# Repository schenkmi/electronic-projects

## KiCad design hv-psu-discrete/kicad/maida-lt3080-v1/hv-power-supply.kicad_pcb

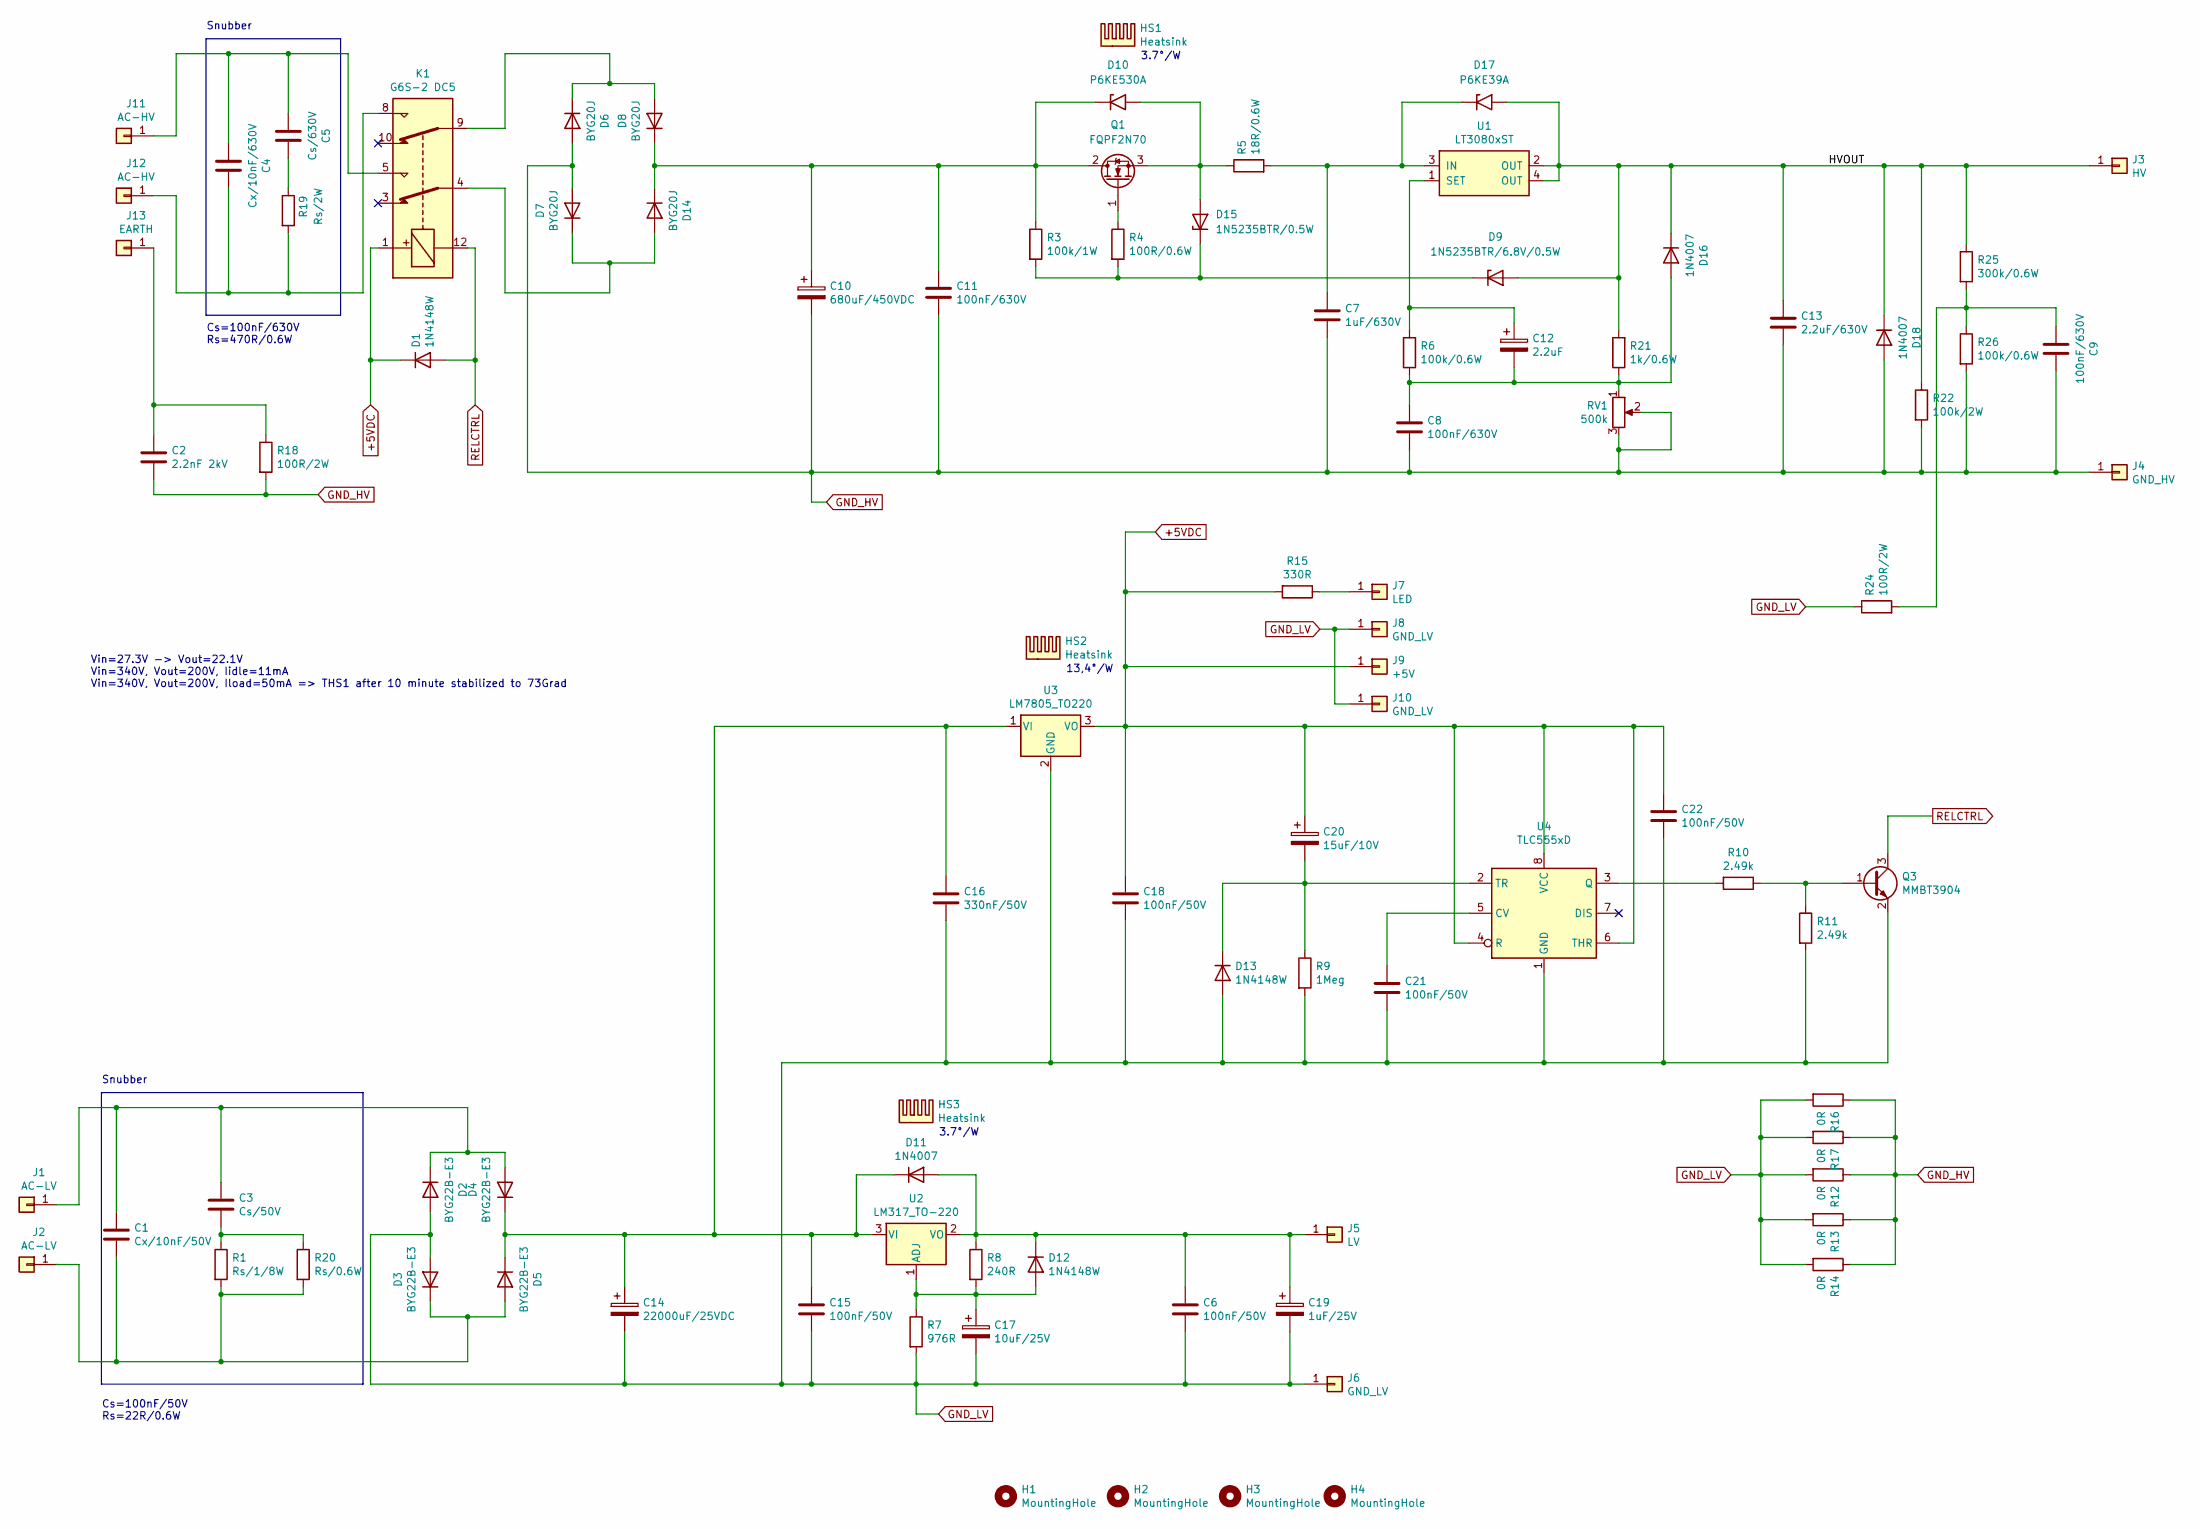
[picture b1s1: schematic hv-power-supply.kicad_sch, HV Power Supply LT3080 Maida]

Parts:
C1: Cx/10nF/50V; C_0805_2012Metric_Pad1.18x1.45mm_HandSolder
C2: 2.2nF 2kV; C_Rect_L18.0mm_W5.0mm_P15.00mm_FKS3_FKP3
C3: Cs/50V; C_0805_2012Metric_Pad1.18x1.45mm_HandSolder
C4: Cx/10nF/630V; C_Rect_L13.0mm_W4.0mm_P10.00mm_FKS3_FKP3_MKS4
C5: Cs/630V; C_Rect_L18.0mm_W5.0mm_P15.00mm_FKS3_FKP3
C6, C15, C18, C21, C22: 100nF/50V; C_0805_2012Metric_Pad1.18x1.45mm_HandSolder
C7: 1uF/630V; C_Rect_L26.5mm_W10.5mm_P22.50mm_MKS4
C8, C9, C11: 100nF/630V; C_Rect_L18.0mm_W5.0mm_P15.00mm_FKS3_FKP3
C10: 680uF/450VDC; CP_Radial_D35.0mm_P10.00mm_SnapIn
C12: 2.2uF; CP_Radial_D5.0mm_P2.50mm
C13: 2.2uF/630V; C_Rect_L33.0mm_W15.0mm_P27.50mm_MKS4
C14: 22000uF/25VDC; CP_Radial_D35.0mm_P10.00mm_SnapIn
C16: 330nF/50V; C_0805_2012Metric_Pad1.18x1.45mm_HandSolder
C17: 10uF/25V; CP_Radial_D5.0mm_P2.00mm
C19: 1uF/25V; CP_Radial_D5.0mm_P2.00mm
C20: 15uF/10V; CP_EIA-3216-12_Kemet-S_Pad1.58x1.35mm_HandSolder
D1, D12, D13: 1N4148W; D_SOD-123
D2, D3, D4, D5: BYG22B-E3; D_SMA_Handsoldering
D6, D7, D8, D14: BYG20J; D_SMA_Handsoldering
D9: 1N5235BTR/6.8V/0.5W; D_DO-35_SOD27_P7.62mm_Horizontal
D10: P6KE530A; D_DO-15_P12.70mm_Horizontal
D11: 1N4007; D_SMA_Handsoldering
D15: 1N5235BTR/0.5W; D_DO-35_SOD27_P7.62mm_Horizontal
D16, D18: 1N4007; D_DO-41_SOD81_P10.16mm_Horizontal
D17: P6KE39A; D_DO-15_P12.70mm_Horizontal
H1, H2, H3, H4: MountingHole; MountingHole_3.2mm_M3
HS1, HS3: Heatsink; Heatsink_Fischer_SK129-STS_42x25mm_2xDrill2.5mm
HS2: Heatsink; Heatsink_Fischer_SK104-STC-STIC_35x13mm_2xDrill2.5mm
J1, J2: AC-LV; Pin_D1.3mm_L11.0mm
J3: HV; Pin_D1.3mm_L11.0mm
J4: GND_HV; Pin_D1.3mm_L11.0mm
J5: LV; Pin_D1.3mm_L11.0mm
J6: GND_LV; Pin_D1.3mm_L11.0mm
J7: LED; Pin_D1.0mm_L10.0mm
J8, J10: GND_LV; Pin_D1.0mm_L10.0mm
J9: +5V; Pin_D1.0mm_L10.0mm
J11, J12: AC-HV; Pin_D1.3mm_L11.0mm
J13: EARTH; Pin_D1.3mm_L11.0mm
K1: G6S-2 DC5; Relay_DPDT_Omron_G6S-2
Q1: FQPF2N70; TO-220-3_Vertical
Q3: MMBT3904; SOT-23
R1: Rs/1/8W; R_0805_2012Metric_Pad1.20x1.40mm_HandSolder
R3: 100k/1W; R_Axial_DIN0207_L6.3mm_D2.5mm_P10.16mm_Horizontal
R4: 100R/0.6W; R_Axial_DIN0207_L6.3mm_D2.5mm_P10.16mm_Horizontal
R5: 18R/0.6W; R_Axial_DIN0207_L6.3mm_D2.5mm_P10.16mm_Horizontal
R6, R26: 100k/0.6W; R_Axial_DIN0207_L6.3mm_D2.5mm_P10.16mm_Horizontal
R7: 976R; R_0805_2012Metric_Pad1.20x1.40mm_HandSolder
R8: 240R; R_0805_2012Metric_Pad1.20x1.40mm_HandSolder
R9: 1Meg; R_0805_2012Metric_Pad1.20x1.40mm_HandSolder
R10, R11: 2.49k; R_0805_2012Metric_Pad1.20x1.40mm_HandSolder
R12, R13, R14, R16, R17: 0R; R_1206_3216Metric_Pad1.30x1.75mm_HandSolder
R15: 330R; R_0805_2012Metric_Pad1.20x1.40mm_HandSolder
R18, R24: 100R/2W; R_Axial_DIN0414_L11.9mm_D4.5mm_P15.24mm_Horizontal
R19: Rs/2W; R_Axial_DIN0414_L11.9mm_D4.5mm_P15.24mm_Horizontal
R20: Rs/0.6W; R_Axial_DIN0207_L6.3mm_D2.5mm_P10.16mm_Horizontal
R21: 1k/0.6W; R_Axial_DIN0207_L6.3mm_D2.5mm_P10.16mm_Horizontal
R22: 100k/2W; R_Axial_DIN0414_L11.9mm_D4.5mm_P15.24mm_Horizontal
R25: 300k/0.6W; R_Axial_DIN0207_L6.3mm_D2.5mm_P10.16mm_Horizontal
RV1: 500k; Potentiometer_Bourns_3296W_Vertical
U1: LT3080xST; SOT-223
U2: LM317_TO-220; TO-220-3_Vertical
U3: LM7805_TO220; TO-220-3_Vertical
U4: TLC555xD; SOIC-8_3.9x4.9mm_P1.27mm

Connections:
+5VDC: C18.1, C20.1, C22.1, D1.1 (K), J9.1, K1.1, R15.2, U3.3 (VO), U4.4 (R), U4.6 (THR), U4.8 (VCC)
/HVOUT: C13.1, D9.2 (A), D16.1 (K), D17.2 (A2), D18.1 (K), J3.1, R21.2, R22.1, R25.1, U1.2 (OUT), U1.4 (OUT)
GND_HV: C2.2, C7.2, C8.2, C9.1, C10.2, C11.2, C13.2, D6.2 (A), D7.2 (A), D18.2 (A), J4.1, R12.1, R13.1, R14.1, R16.1, R17.1, R18.2, R22.2, R26.2, RV1.2, RV1.3
GND_LV: C6.2, C14.2, C15.2, C16.2, C17.2, C18.2, C19.2, C21.2, C22.2, D2.2 (A), D3.2 (A), D13.2 (A), J6.1, J8.1, J10.1, Q3.2 (E), R7.2, R9.2, R11.2, R12.2, R13.2, R14.2, R16.2, R17.2, R24.1, U3.2 (GND), U4.1 (GND)
unnamed: C1.1, C3.1, D2.1 (K), D4.2 (A), J1.1
unnamed: C1.2, D3.1 (K), D5.2 (A), J2.1, R1.2, R20.2
unnamed: C2.1, J13.1, R18.1
unnamed: C3.2, R1.1, R20.1
unnamed: C4.1, J12.1, K1.8, R19.2
unnamed: C4.2, C5.2, J11.1, K1.5
unnamed: C5.1, R19.1
unnamed: C7.1, D17.1 (A1), R5.2, U1.3 (IN)
unnamed: C9.2, R24.2, R25.2, R26.1
unnamed: C10.1, C11.1, D8.1 (K), D10.1 (A1), D14.1 (K), Q1.2 (D), R3.1
unnamed: C12.1, R6.2, U1.1 (SET)
unnamed: C8.1, C12.2, D16.2 (A), R6.1, R21.1, RV1.1
unnamed: C14.1, C15.1, C16.1, D4.1 (K), D5.1 (K), D11.1 (K), U2.3 (VI), U3.1 (VI)
unnamed: C17.1, D12.2 (A), R7.1, R8.2, U2.1 (ADJ)
unnamed: C6.1, C19.1, D11.2 (A), D12.1 (K), J5.1, R8.1, U2.2 (VO)
unnamed: C20.2, D13.1 (K), R9.1, U4.2 (TR)
unnamed: C21.1, U4.5 (CV)
unnamed: D6.1 (K), D8.2 (A), K1.9
unnamed: D10.2 (A2), D15.2 (A), Q1.3 (S), R5.1
unnamed: D7.1 (K), D14.2 (A), K1.4
unnamed: D9.1 (K), D15.1 (K), R3.2, R4.2
unnamed: J7.1, R15.1
unnamed: Q1.1 (G), R4.1
unnamed: Q3.1 (B), R10.1, R11.1
unnamed: R10.2, U4.3 (Q)
RELCTRL: D1.2 (A), K1.12, Q3.3 (C)

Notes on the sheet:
Snubber
Cs=100nF/630V Rs=470R/0.6W
13,4°/W
3.7°/W
Vin=27.3V -> Vout=22.1V Vin=340V, Vout=200V, Iidle=11mA Vin=340V, Vout=200V, Iload=50mA => THS1 after 10 minute stabilized to 73Grad
Cs=100nF/50V Rs=22R/0.6W

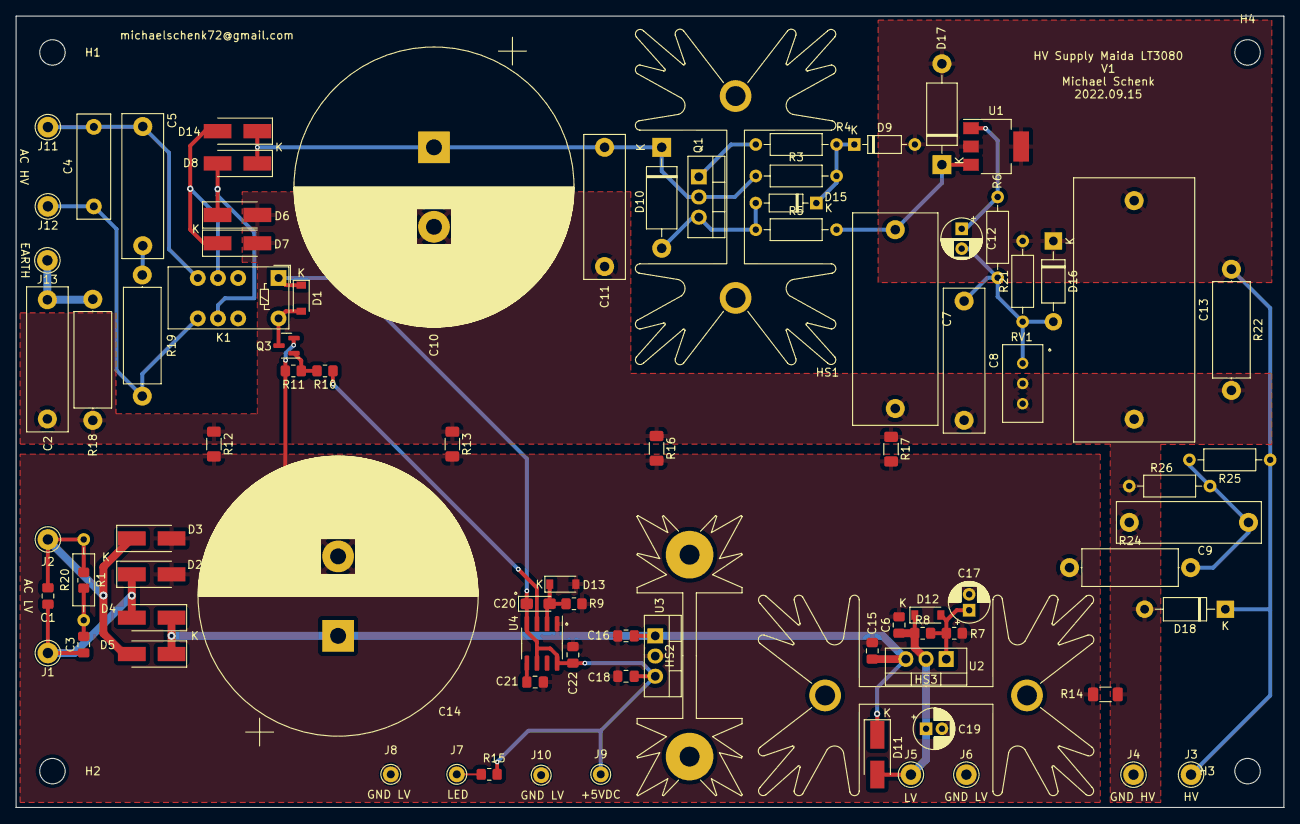
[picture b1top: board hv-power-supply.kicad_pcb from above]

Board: 2 copper layers, 159.5 x 99.6 mm, 92 parts (0 on the bottom side), 30 nets.

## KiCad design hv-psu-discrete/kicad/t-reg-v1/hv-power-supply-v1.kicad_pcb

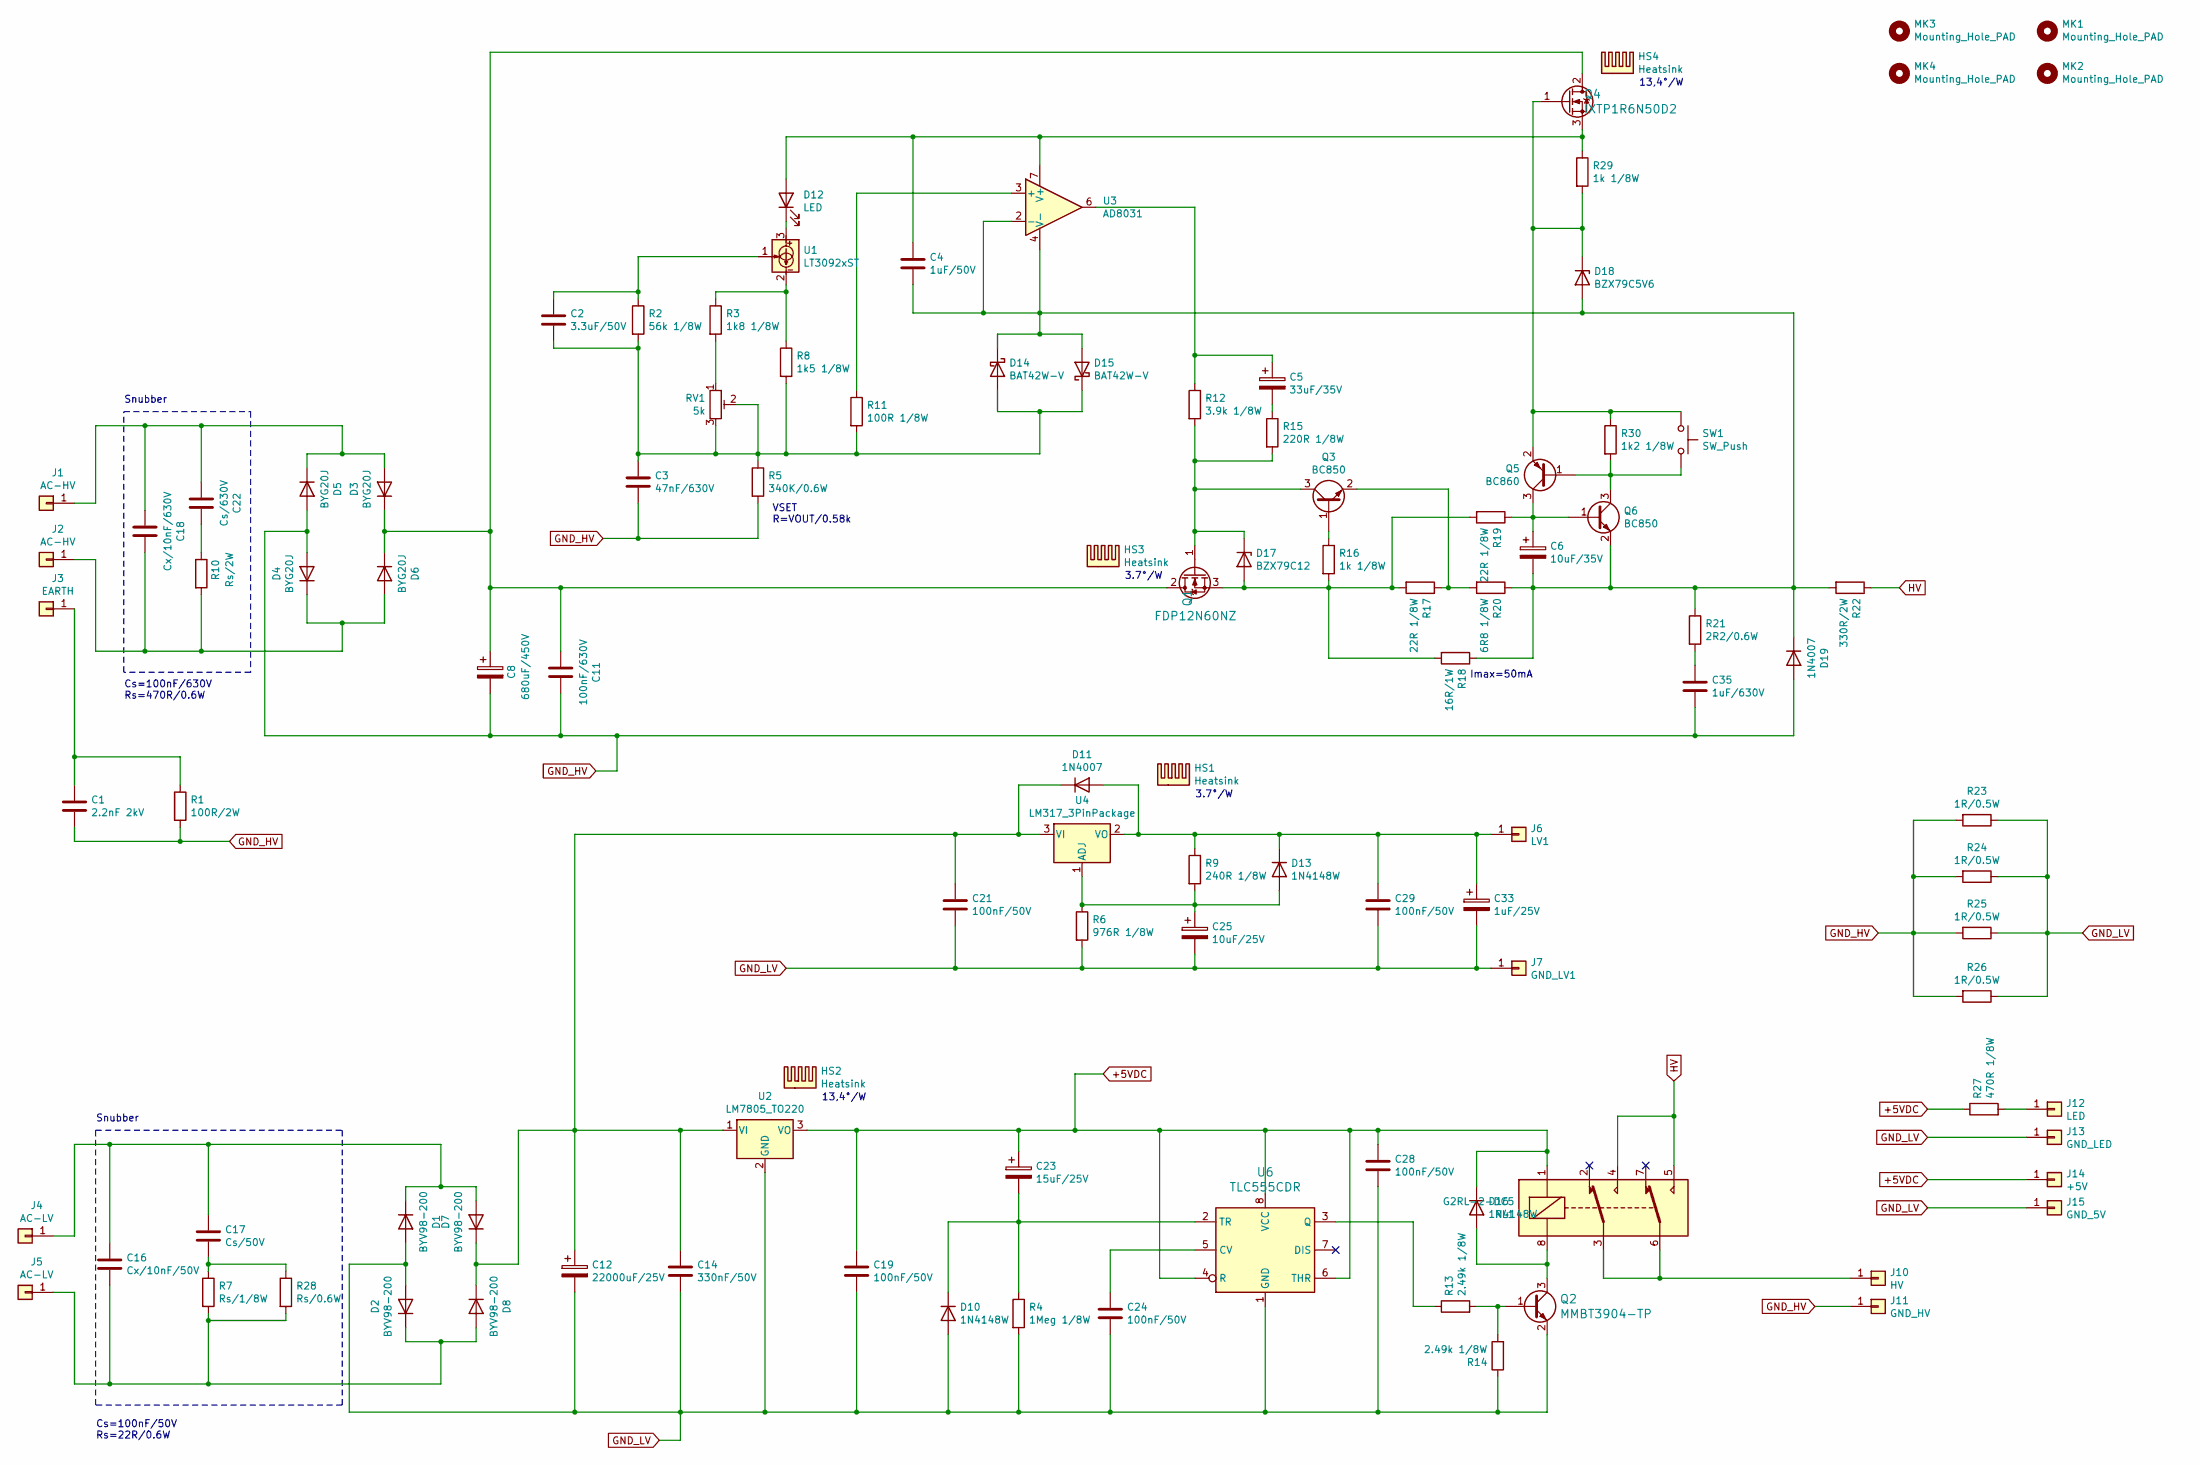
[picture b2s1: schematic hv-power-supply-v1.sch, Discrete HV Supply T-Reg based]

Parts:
C1: 2.2nF 2kV; C_Rect_L18.0mm_W5.0mm_P15.00mm_FKS3_FKP3
C2: 3.3uF/50V; C_1210_3225Metric_Pad1.33x2.70mm_HandSolder
C3: 47nF/630V; C_1210_3225Metric_Pad1.33x2.70mm_HandSolder
C4: 1uF/50V; C_0805_2012Metric_Pad1.18x1.45mm_HandSolder
C5: 33uF/35V; CP_Radial_D5.0mm_P2.00mm
C6: 10uF/35V; CP_Radial_D5.0mm_P2.00mm
C8: 680uF/450V; CP_Radial_D35.0mm_P10.00mm_SnapIn
C11: 100nF/630V; C_Rect_L18.0mm_W5.0mm_P15.00mm_FKS3_FKP3
C12: 22000uF/25V; CP_Radial_D35.0mm_P10.00mm_SnapIn
C14: 330nF/50V; C_0805_2012Metric_Pad1.18x1.45mm_HandSolder
C16: Cx/10nF/50V; C_0805_2012Metric_Pad1.18x1.45mm_HandSolder
C17: Cs/50V; C_0805_2012Metric_Pad1.18x1.45mm_HandSolder
C18: Cx/10nF/630V; C_Rect_L13.0mm_W4.0mm_P10.00mm_FKS3_FKP3_MKS4
C19, C21, C24, C28, C29: 100nF/50V; C_0805_2012Metric_Pad1.18x1.45mm_HandSolder
C22: Cs/630V; C_Rect_L18.0mm_W5.0mm_P15.00mm_FKS3_FKP3
C23: 15uF/25V; CP_EIA-7343-31_Kemet-D_Pad2.25x2.55mm_HandSolder
C25: 10uF/25V; CP_Radial_D5.0mm_P2.00mm
C33: 1uF/25V; CP_Radial_D5.0mm_P2.00mm
C35: 1uF/630V; C_Rect_L26.5mm_W11.5mm_P22.50mm_MKS4
D1, D2, D7, D8: BYV98-200; SOD64-10
D3, D4, D5, D6: BYG20J; D_SMA_Handsoldering
D10, D13, D16: 1N4148W; D_SOD-123
D11, D19: 1N4007; D_SMA_Handsoldering
D12: LED; LED_D3.0mm
D14, D15: BAT42W-V; D_SOD-123
D17: BZX79C12; D_DO-35_SOD27_P7.62mm_Horizontal
D18: BZX79C5V6; D_DO-35_SOD27_P7.62mm_Horizontal
HS1, HS3: Heatsink; Heatsink_Fischer_SK129-STS_42x25mm_2xDrill2.5mm
HS2, HS4: Heatsink; Heatsink_Fischer_SK104-STC-STIC_35x13mm_2xDrill2.5mm
J1, J2: AC-HV; Pin_D1.3mm_L11.0mm
J3: EARTH; Pin_D1.3mm_L11.0mm
J4, J5: AC-LV; Pin_D1.3mm_L11.0mm
J6: LV1; Pin_D1.3mm_L11.0mm
J7: GND_LV1; Pin_D1.3mm_L11.0mm
J10: HV; Pin_D1.3mm_L11.0mm
J11: GND_HV; Pin_D1.3mm_L11.0mm
J12: LED; Pin_D1.0mm_L10.0mm
J13: GND_LED; Pin_D1.0mm_L10.0mm
J14: +5V; Pin_D1.0mm_L10.0mm
J15: GND_5V; Pin_D1.0mm_L10.0mm
MK1, MK2, MK3, MK4: Mounting_Hole_PAD; MountingHole_3.2mm_M3
Q1: FDP12N60NZ; TO-220-3_Vertical; MPN IRF510PBF; Digi-Key_PN IRF510PBF-ND
Q2: MMBT3904-TP; SOT-23; MPN MMBT3904-TP; Digi-Key_PN MMBT3904TPMSCT-ND
Q3, Q6: BC850; SOT-23
Q4: IXTP1R6N50D2; TO-220-3_Vertical; MPN IRF510PBF; Digi-Key_PN IRF510PBF-ND
Q5: BC860; SOT-23
R1: 100R/2W; R_Axial_DIN0414_L11.9mm_D4.5mm_P15.24mm_Horizontal
R2: 56k 1/8W; R_0805_2012Metric_Pad1.20x1.40mm_HandSolder
R3: 1k8 1/8W; R_0805_2012Metric_Pad1.20x1.40mm_HandSolder
R4: 1Meg 1/8W; R_0805_2012Metric_Pad1.20x1.40mm_HandSolder
R5: 340K/0.6W; R_Axial_DIN0207_L6.3mm_D2.5mm_P10.16mm_Horizontal
R6: 976R 1/8W; R_0805_2012Metric_Pad1.20x1.40mm_HandSolder
R7: Rs/1/8W; R_0805_2012Metric_Pad1.20x1.40mm_HandSolder
R8: 1k5 1/8W; R_0805_2012Metric_Pad1.20x1.40mm_HandSolder
R9: 240R 1/8W; R_0805_2012Metric_Pad1.20x1.40mm_HandSolder
R10: Rs/2W; R_Axial_DIN0414_L11.9mm_D4.5mm_P15.24mm_Horizontal
R11: 100R 1/8W; R_0805_2012Metric_Pad1.20x1.40mm_HandSolder
R12: 3.9k 1/8W; R_0805_2012Metric_Pad1.20x1.40mm_HandSolder
R13, R14: 2.49k 1/8W; R_0805_2012Metric_Pad1.20x1.40mm_HandSolder
R15: 220R 1/8W; R_0805_2012Metric_Pad1.20x1.40mm_HandSolder
R16, R29: 1k 1/8W; R_0805_2012Metric_Pad1.20x1.40mm_HandSolder
R17, R19: 22R 1/8W; R_0805_2012Metric_Pad1.20x1.40mm_HandSolder
R18: 16R/1W; R_Axial_DIN0207_L6.3mm_D2.5mm_P10.16mm_Horizontal
R20: 6R8 1/8W; R_0805_2012Metric_Pad1.20x1.40mm_HandSolder
R21: 2R2/0.6W; R_Axial_DIN0207_L6.3mm_D2.5mm_P10.16mm_Horizontal
R22: 330R/2W; R_Axial_DIN0414_L11.9mm_D4.5mm_P15.24mm_Horizontal
R23, R24, R25, R26: 1R/0.5W; R_0805_2012Metric_Pad1.20x1.40mm_HandSolder
R27: 470R 1/8W; R_0805_2012Metric_Pad1.20x1.40mm_HandSolder
R28: Rs/0.6W; R_Axial_DIN0207_L6.3mm_D2.5mm_P10.16mm_Horizontal
R30: 1k2 1/8W; R_0805_2012Metric_Pad1.20x1.40mm_HandSolder
RL1: G2RL-2-DC5; Relay_DPDT_Omron_G2RL
RV1: 5k; Potentiometer_Bourns_3296W_Vertical
SW1: SW_Push; SW_SPST_B3U-1000P
U1: LT3092xST; SOT-223-3_TabPin2
U2: LM7805_TO220; TO-220-3_Vertical
U3: AD8031; SOIC-8_3.9x4.9mm_P1.27mm
U4: LM317_3PinPackage; TO-220-3_Vertical
U6: TLC555CDR; SOIC-8_3.9x4.9mm_P1.27mm; MPN TLC555CDR; Digi-Key_PN 296-1336-1-ND

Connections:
+5VDC: C19.1, C23.1, C28.1, D16.1 (K), J14.1, R27.1, RL1.1, U2.3 (VO), U6.4 (R), U6.6 (THR), U6.8 (VCC)
GND_HV: C1.2, C3.2, C8.2, C11.1, C35.2, D4.2 (A), D5.2 (A), D19.2 (A), J11.1, R1.2, R5.2, R23.2, R24.2, R25.2, R26.2
GND_LV: C12.2, C14.2, C19.2, C21.2, C24.2, C25.2, C28.2, C29.2, C33.2, D1.2 (A), D2.2 (A), D10.2 (A), J7.1, J13.1, J15.1, Q2.2 (E), R4.2, R6.2, R14.1, R23.1, R24.1, R25.1, R26.1, U2.2 (GND), U6.1 (GND)
HV: R22.1, RL1.4, RL1.5
unnamed: C1.1, J3.1, R1.1
unnamed: C2.1, R2.1, U1.1
unnamed: C2.2, C3.1, D14.2 (A), D15.1 (K), R2.2, R5.1, R8.2, R11.2, RV1.2, RV1.3
unnamed: C4.1, D12.2 (A), Q4.3 (S), R29.1, U3.7 (V+)
unnamed: C4.2, C6.2, D14.1 (K), D15.2 (A), D18.2 (A), D19.1 (K), Q6.2 (E), R18.1, R20.1, R21.1, R22.2, U3.2 (-), U3.4 (V-)
unnamed: C5.1, R12.1, U3.6
unnamed: C5.2, R15.1
unnamed: C6.1, Q5.3 (C), Q6.1 (B), R19.1
unnamed: C8.1, C11.2, D3.1 (K), D6.1 (K), Q1.2 (D), Q4.2 (D)
unnamed: C12.1, C14.1, C21.1, D7.1 (K), D8.1 (K), D11.1 (K), U2.1 (VI), U4.3 (VI)
unnamed: C16.1, C17.1, D1.1 (K), D7.2 (A), J4.1
unnamed: C16.2, D2.1 (K), D8.2 (A), J5.1, R7.2, R28.2
unnamed: C17.2, R7.1, R28.1
unnamed: C18.1, D4.1 (K), D6.2 (A), J2.1, R10.2
unnamed: C18.2, C22.2, D3.2 (A), D5.1 (K), J1.1
unnamed: C22.1, R10.1
unnamed: C23.2, D10.1 (K), R4.1, U6.2 (TR)
unnamed: C24.1, U6.5 (CV)
unnamed: C25.1, D13.2 (A), R6.1, R9.2, U4.1 (ADJ)
unnamed: C29.1, C33.1, D11.2 (A), D13.1 (K), J6.1, R9.1, U4.2 (VO)
unnamed: C35.1, R21.2
unnamed: D12.1 (K), U1.3
unnamed: D16.2 (A), Q2.3 (C), RL1.8
unnamed: D17.1 (K), Q1.1 (G), Q3.3 (C), R12.2, R15.2
unnamed: D17.2 (A), Q1.3 (S), R16.2, R17.2, R18.2, R19.2
unnamed: D18.1 (K), Q4.1 (G), Q5.2 (E), R29.2, R30.1, SW1.1
unnamed: J10.1, RL1.3, RL1.6
unnamed: J12.1, R27.2
unnamed: Q2.1 (B), R13.2, R14.2
unnamed: Q3.1 (B), R16.1
unnamed: Q3.2 (E), R17.1, R20.2
unnamed: Q5.1 (B), Q6.3 (C), R30.2, SW1.2
unnamed: R3.1, R8.1, U1.2
unnamed: R3.2, RV1.1
unnamed: R11.1, U3.3 (+)
unnamed: R13.1, U6.3 (Q)

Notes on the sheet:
Snubber
VSET R=VOUT/0.58k
Imax=50mA
Cs=100nF/630V Rs=470R/0.6W
Cs=100nF/50V Rs=22R/0.6W
3.7°/W
13,4°/W

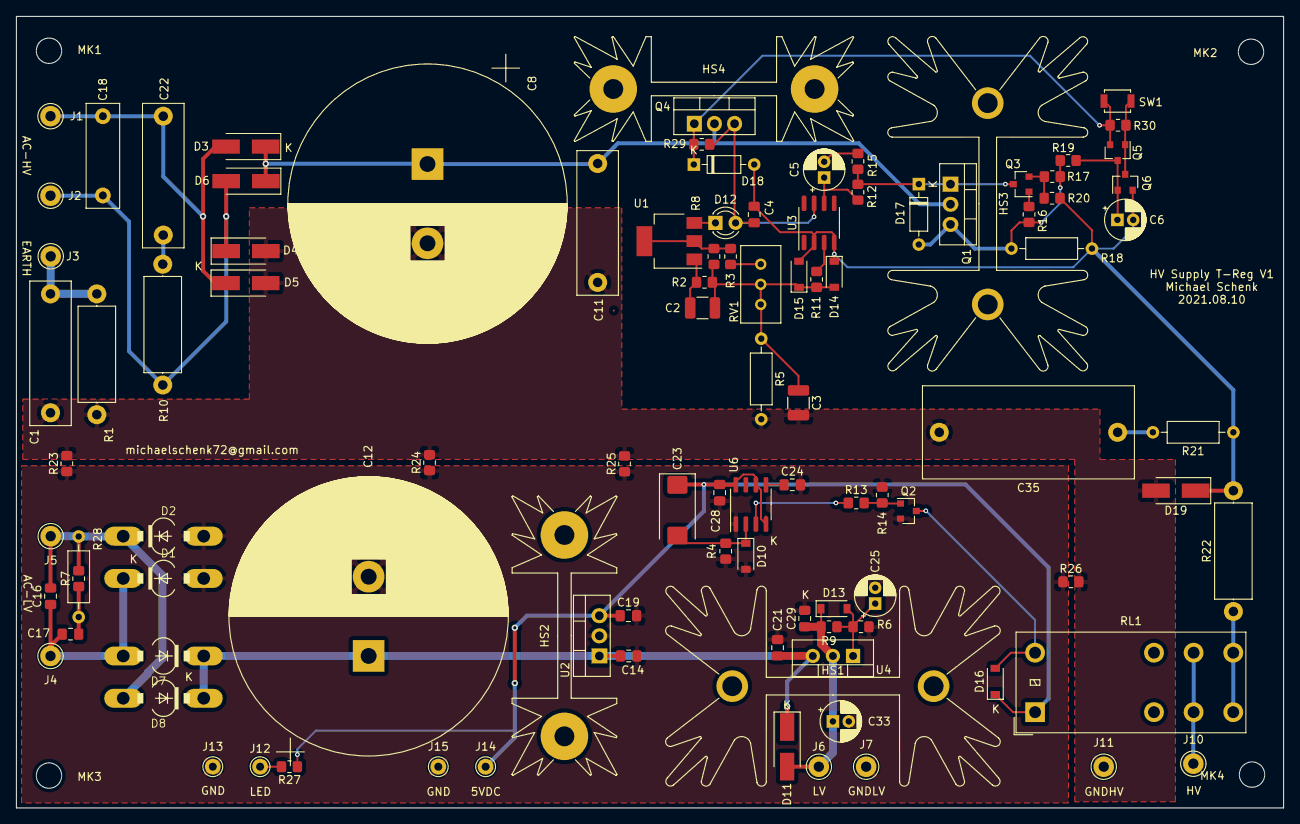
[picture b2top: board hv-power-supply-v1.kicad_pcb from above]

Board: 2 copper layers, 159.9 x 99.9 mm, 106 parts (0 on the bottom side), 40 nets.
